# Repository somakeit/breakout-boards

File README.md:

Breakout Boards
===============
So Make it branded breakout boards to convert SMD parts to 0.1" pin pitch for breadboards.

Copyright So Make It Ltd. 2014.

This documentation describes Open Hardware and is licensed under the CERN OHL v. 1.2.

You may redistribute and modify this documentation under the terms of the CERN OHL v.1.2. (http://ohwr.org/cernohl). This documentation is distributed WITHOUT ANY EXPRESS OR IMPLIED WARRANTY, INCLUDING OF MERCHANTABILITY, SATISFACTORY QUALITY AND FITNESS FOR A PARTICULAR PURPOSE. Please see the CERN OHL v.1.2 for applicable conditions.

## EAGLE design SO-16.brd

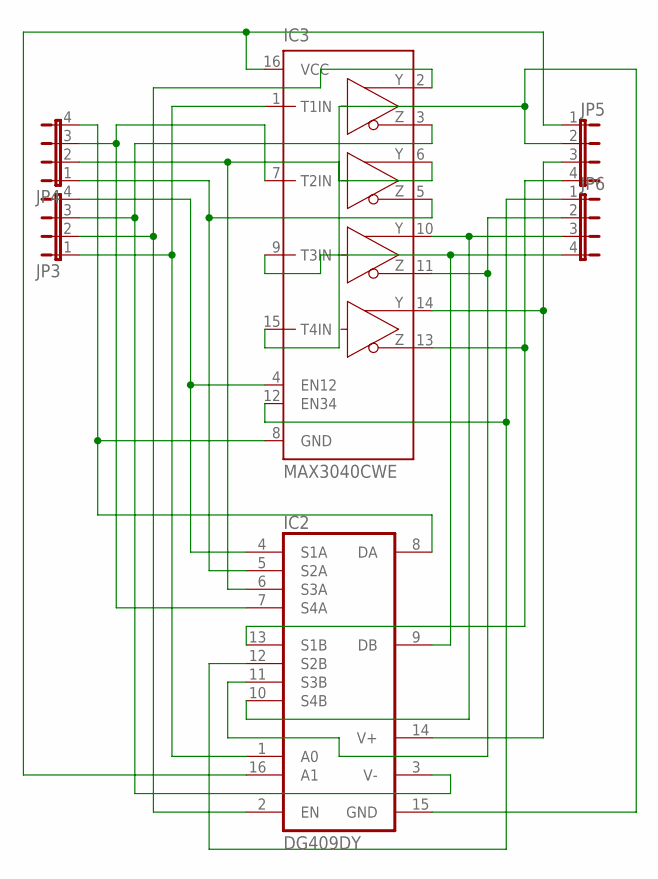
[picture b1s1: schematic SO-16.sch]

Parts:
IC2: DG409DY; SO16
IC3: MAX3040CWE; SO16L
JP3, JP4, JP5, JP6: JP4E; JP4

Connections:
unnamed: IC2.1 (A0), IC3.1 (T1IN), JP3.1
unnamed: IC2.3 (V-), IC3.3 (Z1), JP3.3
unnamed: IC2.2 (EN), IC3.2 (Y1), JP3.2
unnamed: IC2.4 (S1A), IC3.4 (EN12), JP3.4
unnamed: IC2.5 (S2A), IC3.5 (Z2), JP4.1
unnamed: IC2.6 (S3A), IC3.6 (Y2), JP4.2
unnamed: IC2.7 (S4A), IC3.7 (T2IN), JP4.3
unnamed: IC2.8 (DA), IC3.8 (GND), JP4.4
unnamed: IC2.13 (S1B), IC3.13 (Z4), JP5.4
unnamed: IC2.9 (DB), IC3.9 (T3IN), JP6.4
unnamed: IC2.10 (S4B), IC3.10 (Y3), JP6.3
unnamed: IC2.12 (S2B), IC3.12 (EN34), JP6.1
unnamed: IC2.11 (S3B), IC3.11 (Z3), JP6.2
unnamed: IC2.15 (GND), IC3.15 (T4IN), JP5.2
unnamed: IC2.14 (V+), IC3.14 (Y4), JP5.3
unnamed: IC2.16 (A1), IC3.16 (VCC), JP5.1

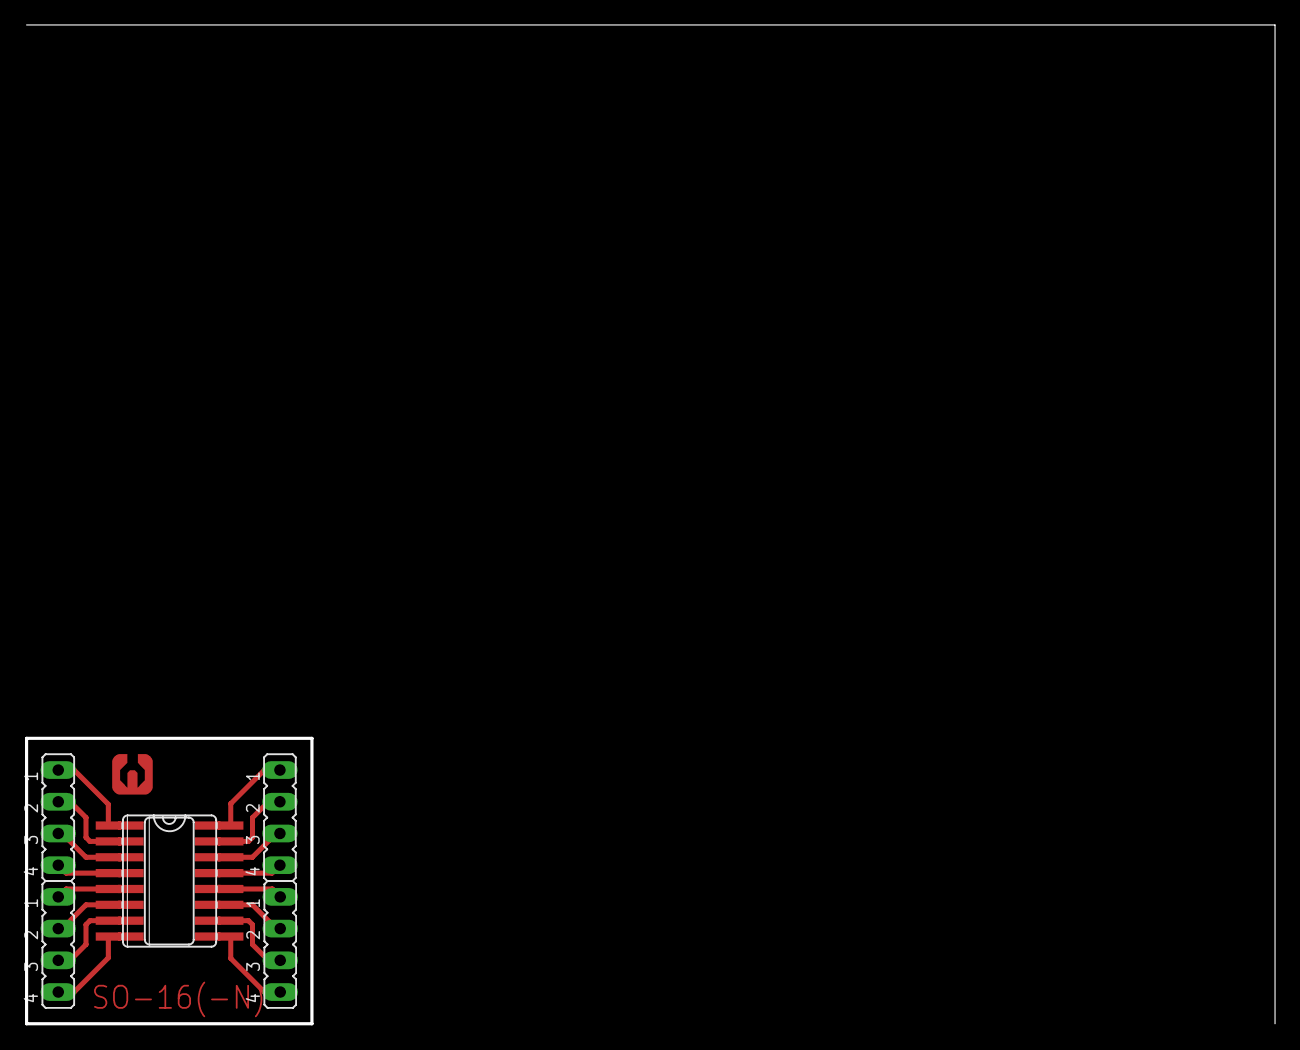
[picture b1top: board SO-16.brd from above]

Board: 2 copper layers, 22.9 x 22.9 mm, 6 parts (0 on the bottom side), 16 nets.

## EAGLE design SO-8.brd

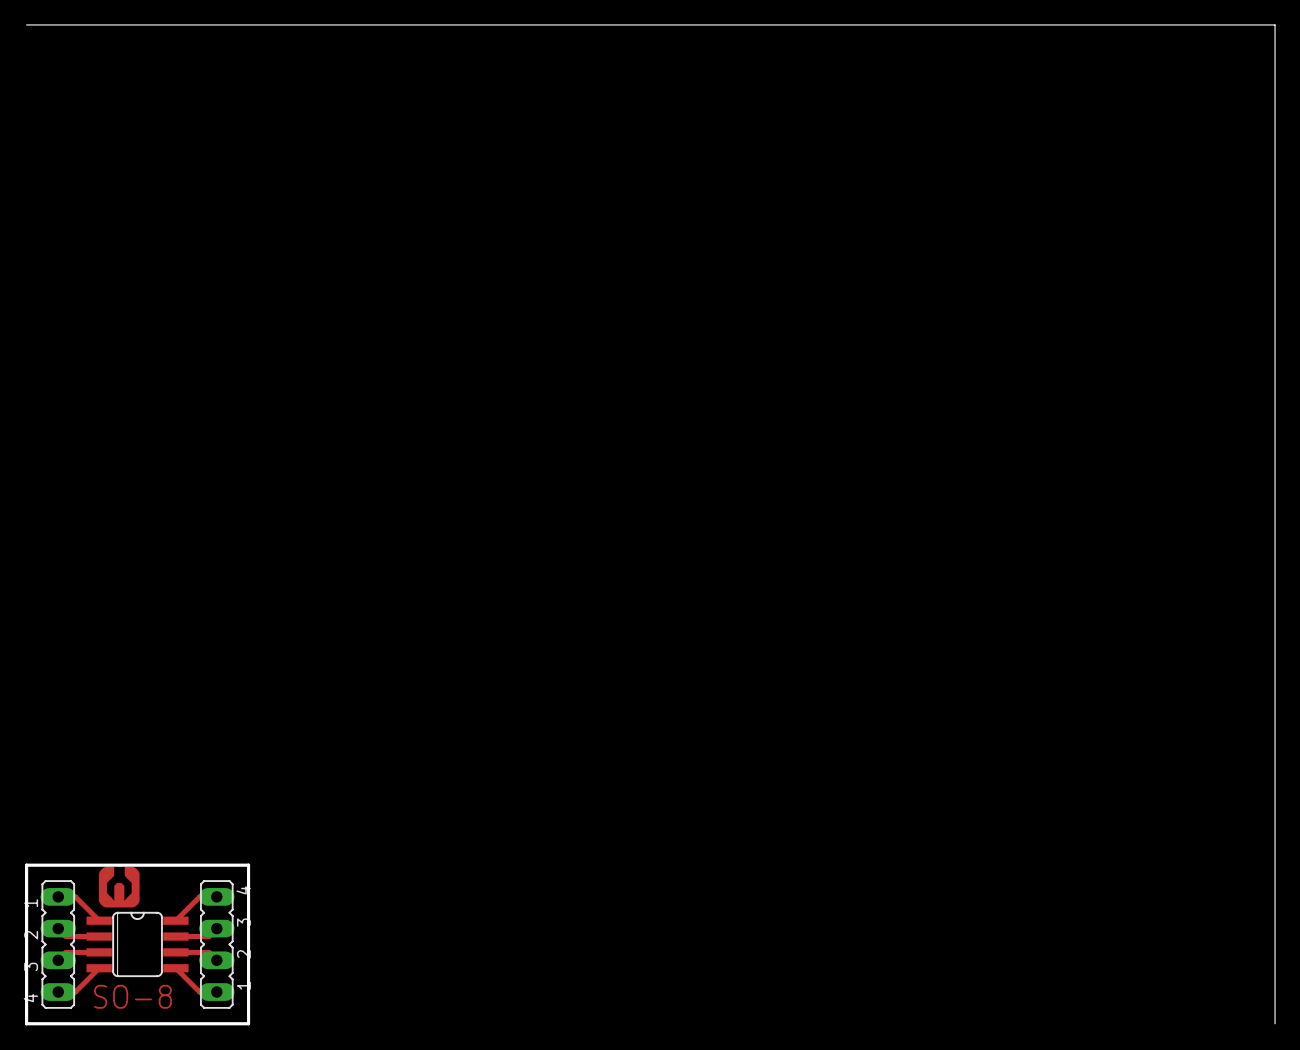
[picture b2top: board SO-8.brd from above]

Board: 2 copper layers, 17.8 x 12.7 mm, 3 parts (0 on the bottom side), 8 nets.

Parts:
IC1: SO08
JP1, JP2: JP4

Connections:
unnamed: IC1.1, JP1.1
unnamed: IC1.2, JP1.2
unnamed: IC1.3, JP1.3
unnamed: IC1.4, JP1.4
unnamed: IC1.5, JP2.1
unnamed: IC1.6, JP2.2
unnamed: IC1.7, JP2.3
unnamed: IC1.8, JP2.4

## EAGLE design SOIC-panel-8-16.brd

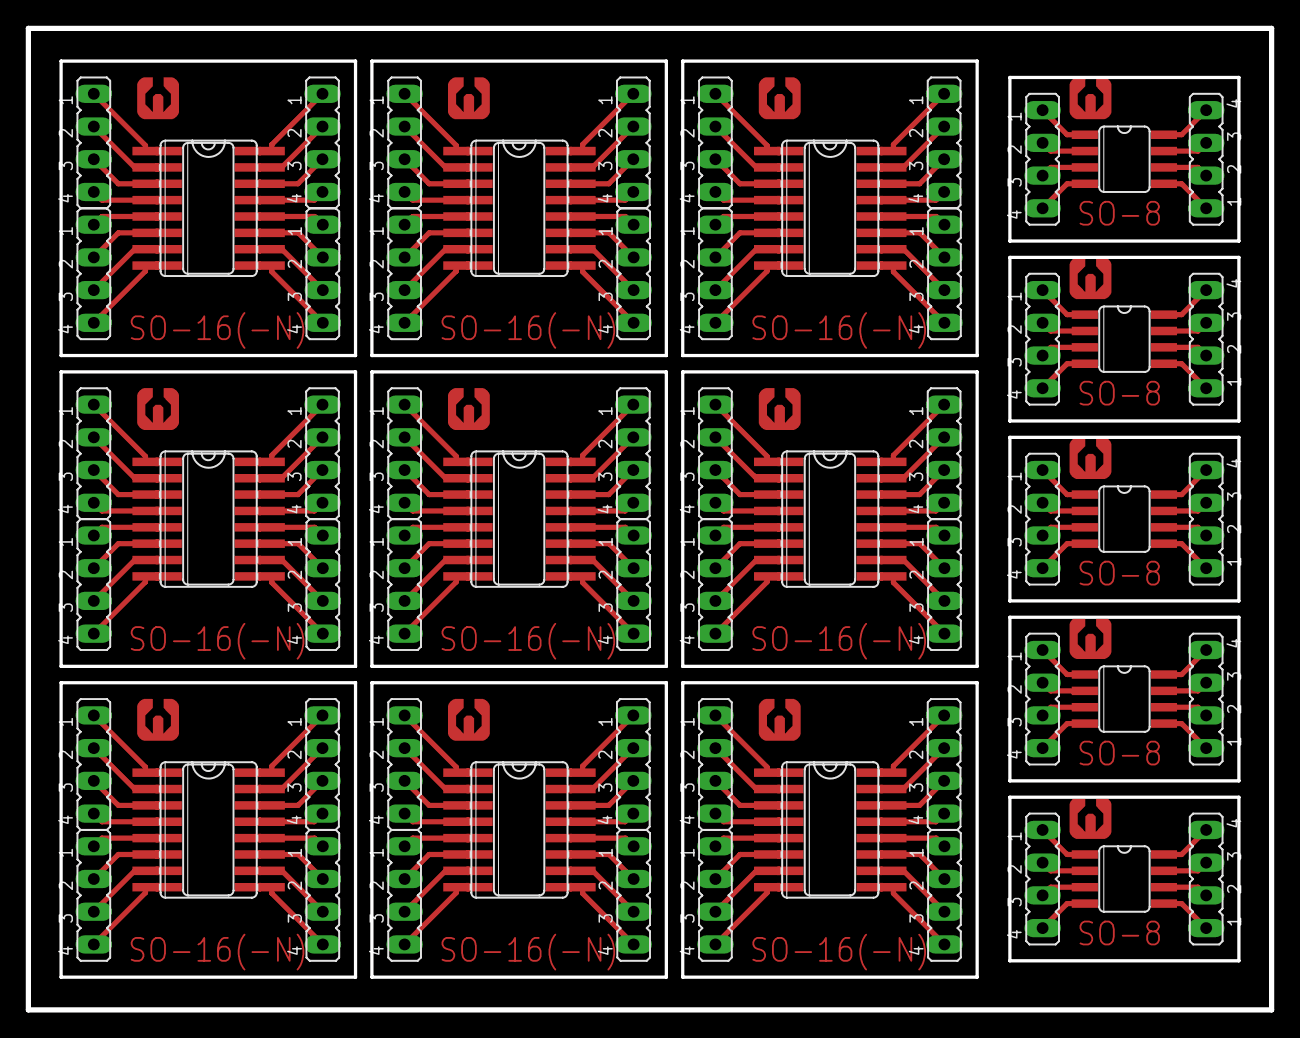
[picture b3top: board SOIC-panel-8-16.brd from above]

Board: 2 copper layers, 96.5 x 76.2 mm, 69 parts (0 on the bottom side), 184 nets.

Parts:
IC1, IC20, IC21, IC22, IC23: SO08
IC2, IC5, IC7, IC9, IC11, IC13, IC15, IC17, IC19: DG409DY; SO16
IC3, IC4, IC6, IC8, IC10, IC12, IC14, IC16, IC18: MAX3040CWE; SO16L
JP1, JP2, JP3, JP4, JP5, JP6, JP7, JP8, JP9, JP10, JP11, JP12, JP13, JP14, JP15, JP16, JP17, JP18, JP19, JP20, JP21, JP22, JP23, JP24, JP25, JP26, JP27, JP28, JP29, JP30, JP31, JP32, JP33, JP34, JP35, JP36, JP37, JP38, JP39, JP40, JP41, JP42, JP43, JP44, JP45, JP46: JP4

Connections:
unnamed: IC1.1, JP1.1
unnamed: IC1.2, JP1.2
unnamed: IC1.3, JP1.3
unnamed: IC1.4, JP1.4
unnamed: IC1.5, JP2.1
unnamed: IC1.6, JP2.2
unnamed: IC1.7, JP2.3
unnamed: IC2.1, IC3.1, JP3.1
unnamed: IC1.8, JP2.4
unnamed: IC2.3, IC3.3, JP3.3
unnamed: IC2.2, IC3.2, JP3.2
unnamed: IC2.4, IC3.4, JP3.4
unnamed: IC2.5, IC3.5, JP4.1
unnamed: IC2.6, IC3.6, JP4.2
unnamed: IC2.7, IC3.7, JP4.3
unnamed: IC2.8, IC3.8, JP4.4
unnamed: IC2.13, IC3.13, JP5.4
unnamed: IC2.9, IC3.9, JP6.4
unnamed: IC2.10, IC3.10, JP6.3
unnamed: IC2.12, IC3.12, JP6.1
unnamed: IC2.11, IC3.11, JP6.2
unnamed: IC2.15, IC3.15, JP5.2
unnamed: IC2.14, IC3.14, JP5.3
unnamed: IC4.1, IC5.1, JP7.1
unnamed: IC2.16, IC3.16, JP5.1
unnamed: IC4.2, IC5.2, JP7.2
unnamed: IC4.3, IC5.3, JP7.3
unnamed: IC4.4, IC5.4, JP7.4
unnamed: IC4.5, IC5.5, JP8.1
unnamed: IC4.6, IC5.6, JP8.2
unnamed: IC4.7, IC5.7, JP8.3
unnamed: IC4.8, IC5.8, JP8.4
unnamed: IC4.9, IC5.9, JP10.4
unnamed: IC4.10, IC5.10, JP10.3
unnamed: IC4.11, IC5.11, JP10.2
unnamed: IC4.12, IC5.12, JP10.1
unnamed: IC4.13, IC5.13, JP9.4
unnamed: IC4.14, IC5.14, JP9.3
unnamed: IC4.15, IC5.15, JP9.2
unnamed: IC4.16, IC5.16, JP9.1
unnamed: IC6.1, IC7.1, JP11.1
unnamed: IC6.2, IC7.2, JP11.2
unnamed: IC6.3, IC7.3, JP11.3
unnamed: IC6.4, IC7.4, JP11.4
unnamed: IC6.5, IC7.5, JP12.1
unnamed: IC6.6, IC7.6, JP12.2
unnamed: IC6.7, IC7.7, JP12.3
unnamed: IC6.8, IC7.8, JP12.4
unnamed: IC6.9, IC7.9, JP14.4
unnamed: IC6.10, IC7.10, JP14.3
unnamed: IC6.11, IC7.11, JP14.2
unnamed: IC6.12, IC7.12, JP14.1
unnamed: IC6.13, IC7.13, JP13.4
unnamed: IC6.14, IC7.14, JP13.3
unnamed: IC6.15, IC7.15, JP13.2
unnamed: IC6.16, IC7.16, JP13.1
unnamed: IC8.1, IC9.1, JP15.1
unnamed: IC8.2, IC9.2, JP15.2
unnamed: IC8.3, IC9.3, JP15.3
unnamed: IC8.4, IC9.4, JP15.4
unnamed: IC8.5, IC9.5, JP16.1
unnamed: IC8.6, IC9.6, JP16.2
unnamed: IC8.7, IC9.7, JP16.3
unnamed: IC8.8, IC9.8, JP16.4
unnamed: IC8.9, IC9.9, JP18.4
unnamed: IC8.10, IC9.10, JP18.3
unnamed: IC8.11, IC9.11, JP18.2
unnamed: IC8.12, IC9.12, JP18.1
unnamed: IC8.13, IC9.13, JP17.4
unnamed: IC8.14, IC9.14, JP17.3
unnamed: IC8.15, IC9.15, JP17.2
unnamed: IC8.16, IC9.16, JP17.1
unnamed: IC10.1, IC11.1, JP19.1
unnamed: IC10.2, IC11.2, JP19.2
unnamed: IC10.3, IC11.3, JP19.3
unnamed: IC10.4, IC11.4, JP19.4
unnamed: IC10.5, IC11.5, JP20.1
unnamed: IC10.6, IC11.6, JP20.2
unnamed: IC10.7, IC11.7, JP20.3
unnamed: IC10.8, IC11.8, JP20.4
unnamed: IC10.9, IC11.9, JP22.4
unnamed: IC10.10, IC11.10, JP22.3
unnamed: IC10.11, IC11.11, JP22.2
unnamed: IC10.12, IC11.12, JP22.1
unnamed: IC10.13, IC11.13, JP21.4
unnamed: IC10.14, IC11.14, JP21.3
unnamed: IC10.15, IC11.15, JP21.2
unnamed: IC10.16, IC11.16, JP21.1
unnamed: IC12.1, IC13.1, JP23.1
unnamed: IC12.2, IC13.2, JP23.2
unnamed: IC12.3, IC13.3, JP23.3
unnamed: IC12.4, IC13.4, JP23.4
unnamed: IC12.5, IC13.5, JP24.1
unnamed: IC12.6, IC13.6, JP24.2
unnamed: IC12.7, IC13.7, JP24.3
unnamed: IC12.8, IC13.8, JP24.4
unnamed: IC12.9, IC13.9, JP26.4
unnamed: IC12.10, IC13.10, JP26.3
unnamed: IC12.11, IC13.11, JP26.2
unnamed: IC12.12, IC13.12, JP26.1
unnamed: IC12.13, IC13.13, JP25.4
unnamed: IC12.14, IC13.14, JP25.3
unnamed: IC12.15, IC13.15, JP25.2
unnamed: IC12.16, IC13.16, JP25.1
unnamed: IC14.1, IC15.1, JP27.1
unnamed: IC14.2, IC15.2, JP27.2
unnamed: IC14.3, IC15.3, JP27.3
unnamed: IC14.4, IC15.4, JP27.4
unnamed: IC14.5, IC15.5, JP28.1
unnamed: IC14.6, IC15.6, JP28.2
unnamed: IC14.7, IC15.7, JP28.3
unnamed: IC14.8, IC15.8, JP28.4
unnamed: IC14.9, IC15.9, JP30.4
unnamed: IC14.10, IC15.10, JP30.3
unnamed: IC14.11, IC15.11, JP30.2
unnamed: IC14.12, IC15.12, JP30.1
unnamed: IC14.13, IC15.13, JP29.4
unnamed: IC14.14, IC15.14, JP29.3
unnamed: IC14.15, IC15.15, JP29.2
unnamed: IC14.16, IC15.16, JP29.1
unnamed: IC16.1, IC17.1, JP31.1
unnamed: IC16.2, IC17.2, JP31.2
unnamed: IC16.3, IC17.3, JP31.3
unnamed: IC16.4, IC17.4, JP31.4
unnamed: IC16.5, IC17.5, JP32.1
unnamed: IC16.6, IC17.6, JP32.2
unnamed: IC16.7, IC17.7, JP32.3
unnamed: IC16.8, IC17.8, JP32.4
unnamed: IC16.9, IC17.9, JP34.4
unnamed: IC16.10, IC17.10, JP34.3
unnamed: IC16.11, IC17.11, JP34.2
unnamed: IC16.12, IC17.12, JP34.1
unnamed: IC16.13, IC17.13, JP33.4
unnamed: IC16.14, IC17.14, JP33.3
unnamed: IC16.15, IC17.15, JP33.2
unnamed: IC16.16, IC17.16, JP33.1
unnamed: IC18.1, IC19.1, JP35.1
unnamed: IC18.2, IC19.2, JP35.2
unnamed: IC18.3, IC19.3, JP35.3
unnamed: IC18.4, IC19.4, JP35.4
unnamed: IC18.5, IC19.5, JP36.1
unnamed: IC18.6, IC19.6, JP36.2
unnamed: IC18.7, IC19.7, JP36.3
unnamed: IC18.8, IC19.8, JP36.4
unnamed: IC18.9, IC19.9, JP38.4
unnamed: IC18.10, IC19.10, JP38.3
unnamed: IC18.11, IC19.11, JP38.2
unnamed: IC18.12, IC19.12, JP38.1
unnamed: IC18.13, IC19.13, JP37.4
unnamed: IC18.14, IC19.14, JP37.3
unnamed: IC18.15, IC19.15, JP37.2
unnamed: IC18.16, IC19.16, JP37.1
unnamed: IC20.1, JP39.1
unnamed: IC20.2, JP39.2
unnamed: IC20.3, JP39.3
unnamed: IC20.4, JP39.4
unnamed: IC20.5, JP40.1
unnamed: IC20.6, JP40.2
unnamed: IC20.7, JP40.3
unnamed: IC20.8, JP40.4
unnamed: IC21.1, JP41.1
unnamed: IC21.2, JP41.2
unnamed: IC21.3, JP41.3
unnamed: IC21.4, JP41.4
unnamed: IC21.5, JP42.1
unnamed: IC21.6, JP42.2
unnamed: IC21.7, JP42.3
unnamed: IC21.8, JP42.4
unnamed: IC22.1, JP43.1
unnamed: IC22.2, JP43.2
unnamed: IC22.3, JP43.3
unnamed: IC22.4, JP43.4
unnamed: IC22.5, JP44.1
unnamed: IC22.6, JP44.2
unnamed: IC22.7, JP44.3
unnamed: IC22.8, JP44.4
unnamed: IC23.1, JP45.1
unnamed: IC23.2, JP45.2
unnamed: IC23.3, JP45.3
unnamed: IC23.4, JP45.4
unnamed: IC23.5, JP46.1
unnamed: IC23.6, JP46.2
unnamed: IC23.7, JP46.3
unnamed: IC23.8, JP46.4

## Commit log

2014-10-23 First post!!!!!!!!!!!!!
    SO-8, SO-16 and SO-16-N
2014-10-23 Add docs and license
2014-10-23 Fix image?
2014-10-23 Really fix image
2014-10-23 really really really fix image
2014-10-30 Increase trace clearance
    The boards I made had a few shorts.
